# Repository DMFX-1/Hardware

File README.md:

# Hardware
Digital Multi FX Hardware:

DMFX-1 => Motherboard
DMFX-2 => Mezzanine board
Meca => Mechanics
  3D Models => 3D models for electronics 

- Block diagram (image, SVG)
- 3D models (FreeCad, STEP)
- Schematics (Eagle CAD, PDF) 
- PCB layout (Eagle CAD, gerbers)
- BoM (Excel, CSV, text)

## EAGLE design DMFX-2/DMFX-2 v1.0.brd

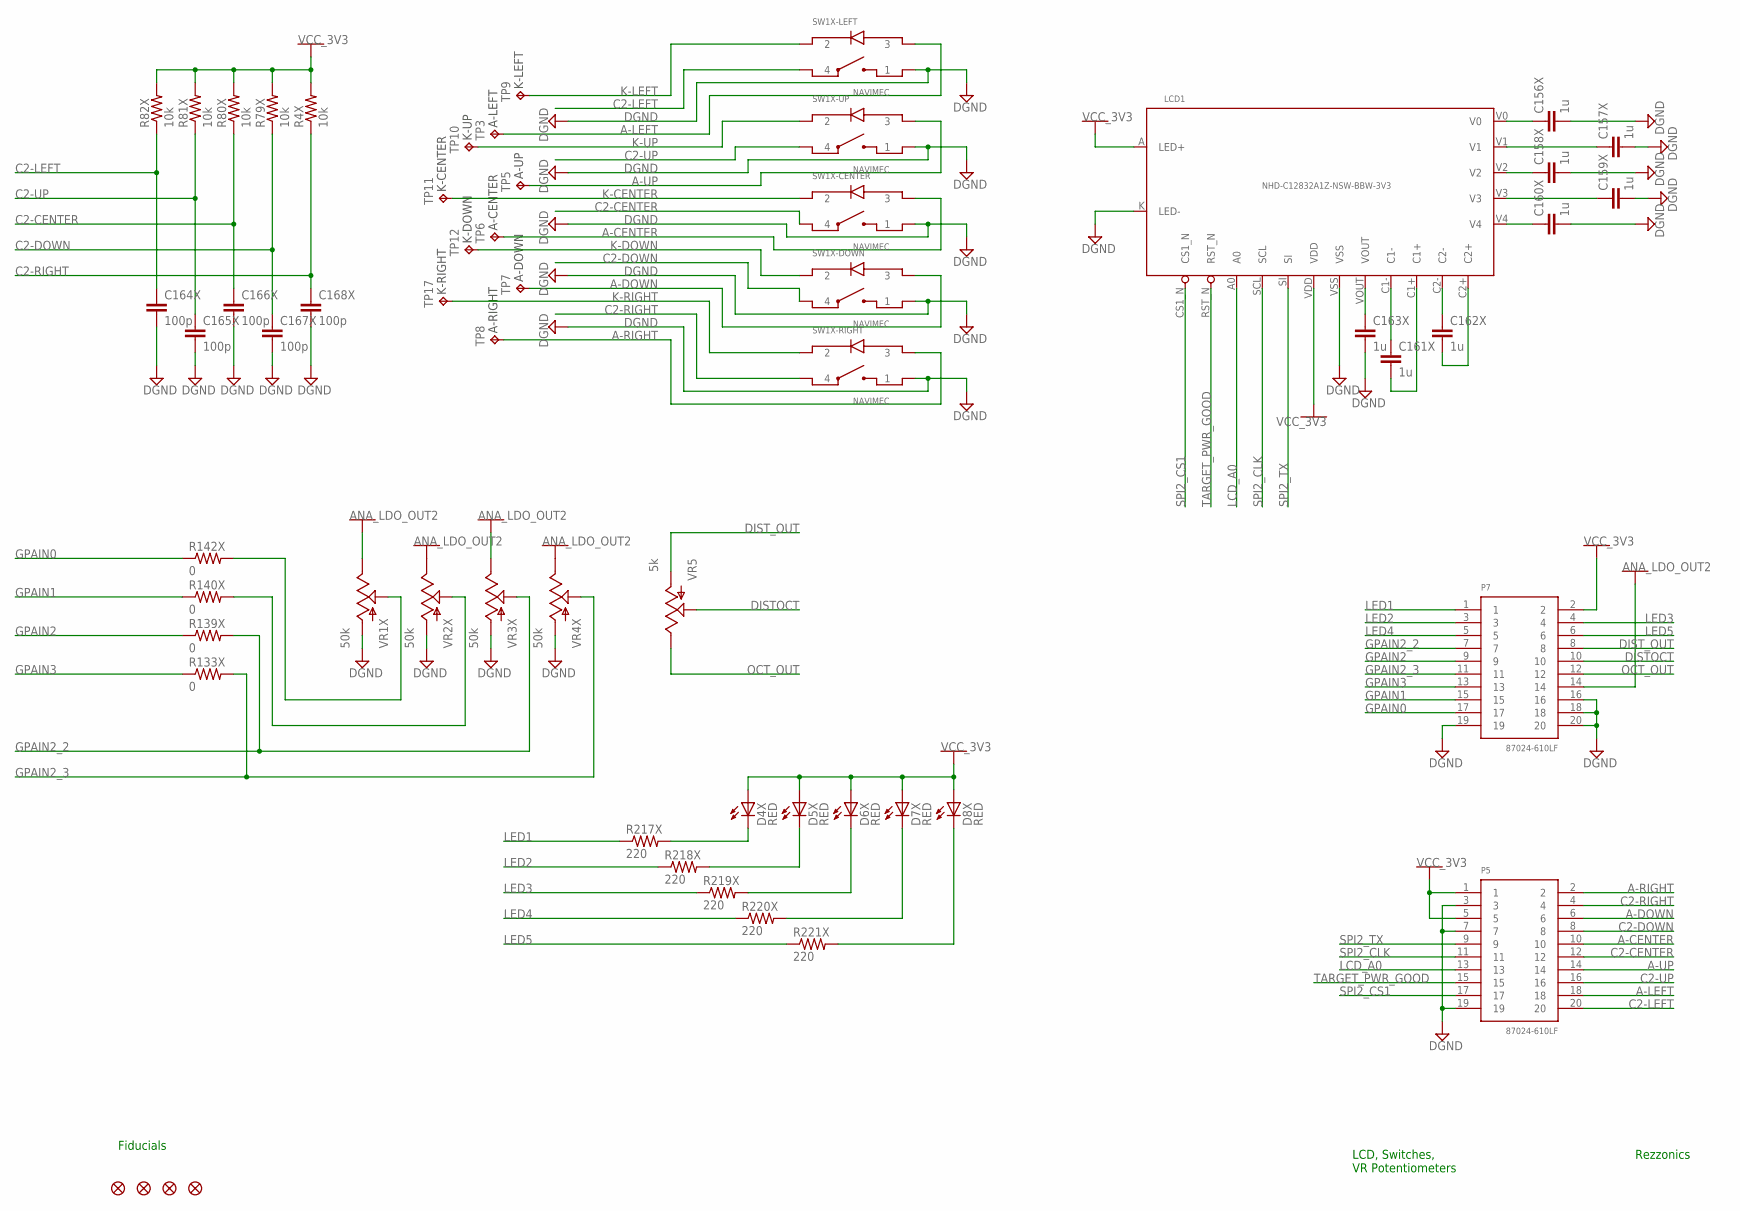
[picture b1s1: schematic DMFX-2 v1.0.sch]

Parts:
C156X, C157X, C158X, C159X, C160X, C161X, C162X, C163X: 1u; C0603K; MPN GRM188R7YA105KA12D
C164X, C165X, C166X, C167X, C168X: 100p; C0402; MPN GRM1555C1H101FA01J
D4X, D5X, D6X, D7X, D8X: RED; LED3MM; MPN LTL-4222N
JP2, JP4, JP5, JP9: FIDUCIAL1X2.5; FIDUCIAL-1X2.5; MPN *
LCD1: NHD-C12832A1Z-NSW-BBW-3V3; NHD-C12832A1Z; MPN NHD-C12832A1Z-NSW-BBW-3V3
P5, P7: 87024-610LF; 87022-110LF; MPN 87024-610LF
R4X, R79X, R80X, R81X, R82X: 10k; 0402-RES; MPN ERJ-2RKF1002X
R133X, R139X, R140X, R142X: 0; 0402-RES; MPN ERJ-2GE0R00X
R217X, R218X, R219X, R220X, R221X: 220; 0402-RES; MPN ERJ-2RKF2200X
SW1X: NAVIMEC; 1ZW0913611806; MPN 1ZW0913611806
TP3, TP5, TP6, TP7, TP8, TP9, TP10, TP11, TP12, TP17: TPTP12R; TP12R; MPN *
VR1X, VR2X, VR3X, VR4X: 50k; ALPS_POT; MPN EVU-F2AF30B54
VR5: 5k; ALPS_POT; MPN EVU-F2AF30B53

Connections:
A-CENTER: P5.10, SW1X.CENTER$3 (3), TP6.TP
A-DOWN: P5.6, SW1X.DOWN$3 (3), TP7.TP
A-LEFT: P5.18, SW1X.LEFT$3 (3), TP3.TP
A-RIGHT: P5.2, SW1X.RIGHT$3 (3), TP8.TP
A-UP: P5.14, SW1X.UP$3 (3), TP5.TP
ANA_LDO_OUT2: P7.14, VR1X.P$1 (E), VR2X.P$1 (E), VR3X.P$1 (E), VR4X.P$1 (E)
C2-CENTER: C166X.1, P5.12, R80X.1, SW1X.CENTER$4 (4)
C2-DOWN: C167X.1, P5.8, R79X.1, SW1X.DOWN$4 (4)
C2-LEFT: C164X.1, P5.20, R82X.1, SW1X.LEFT$4 (4)
C2-RIGHT: C168X.1, P5.4, R4X.1, SW1X.RIGHT$4 (4)
C2-UP: C165X.1, P5.16, R81X.1, SW1X.UP$4 (4)
DGND: C156X.2, C157X.2, C158X.2, C159X.2, C160X.2, C163X.2, C164X.2, C165X.2, C166X.2, C167X.2, C168X.2, LCD1.K (LED-), LCD1.VSS, P5.3, P5.7, P5.19, P7.16, P7.18, P7.19, P7.20, SW1X.CENTER$1 (1), SW1X.DOWN$1 (1), SW1X.LEFT$1 (1), SW1X.RIGHT$1 (1), SW1X.UP$1 (1), VR1X.P$3 (A), VR2X.P$3 (A), VR3X.P$3 (A), VR4X.P$3 (A)
DISTOCT: P7.10, VR5.P$2 (S)
DIST_OUT: P7.8, VR5.P$3 (A)
GPAIN0: P7.17, R142X.1
GPAIN1: P7.15, R140X.1
GPAIN2: P7.9, R139X.1
GPAIN2_0: R142X.2, VR1X.P$2 (S)
GPAIN2_1: R140X.2, VR2X.P$2 (S)
GPAIN2_2: P7.7, R139X.2, VR3X.P$2 (S)
GPAIN2_3: P7.11, R133X.2, VR4X.P$2 (S)
GPAIN3: P7.13, R133X.1
K-CENTER: SW1X.CENTER$2 (2), TP11.TP
K-DOWN: SW1X.DOWN$2 (2), TP12.TP
K-LEFT: SW1X.LEFT$2 (2), TP9.TP
K-RIGHT: SW1X.RIGHT$2 (2), TP17.TP
K-UP: SW1X.UP$2 (2), TP10.TP
LCD_A0: LCD1.A0, P5.13
LCD_C1+: C161X.2, LCD1.C1+
LCD_C1-: C161X.1, LCD1.C1-
LCD_C2+: C162X.2, LCD1.C2+
LCD_C2-: C162X.1, LCD1.C2-
LCD_V0: C156X.1, LCD1.V0
LCD_V1: C157X.1, LCD1.V1
LCD_V2: C158X.1, LCD1.V2
LCD_V3: C159X.1, LCD1.V3
LCD_V4: C160X.1, LCD1.V4
LCD_VOUT: C163X.1, LCD1.VOUT
LED1: P7.1, R217X.1
LED2: P7.3, R218X.1
LED3: P7.4, R219X.1
LED4: P7.5, R220X.1
LED5: P7.6, R221X.1
unnamed: D4X.K (C), R217X.2
unnamed: D5X.K (C), R218X.2
unnamed: D6X.K (C), R219X.2
unnamed: D7X.K (C), R220X.2
unnamed: D8X.K (C), R221X.2
OCT_OUT: P7.12, VR5.P$1 (E)
SPI2_CLK: LCD1.SCL, P5.11
SPI2_CS1: LCD1.CS1_N, P5.17
SPI2_TX: LCD1.SI, P5.9
TARGET_PWR_GOOD: LCD1.RST_N, P5.15
VCC_3V3: D4X.A, D5X.A, D6X.A, D7X.A, D8X.A, LCD1.A (LED+), LCD1.VDD, P5.1, P5.5, P7.2, R4X.2, R79X.2, R80X.2, R81X.2, R82X.2

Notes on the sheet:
Rezzonics
LCD, Switches, VR Potentiometers
Fiducials

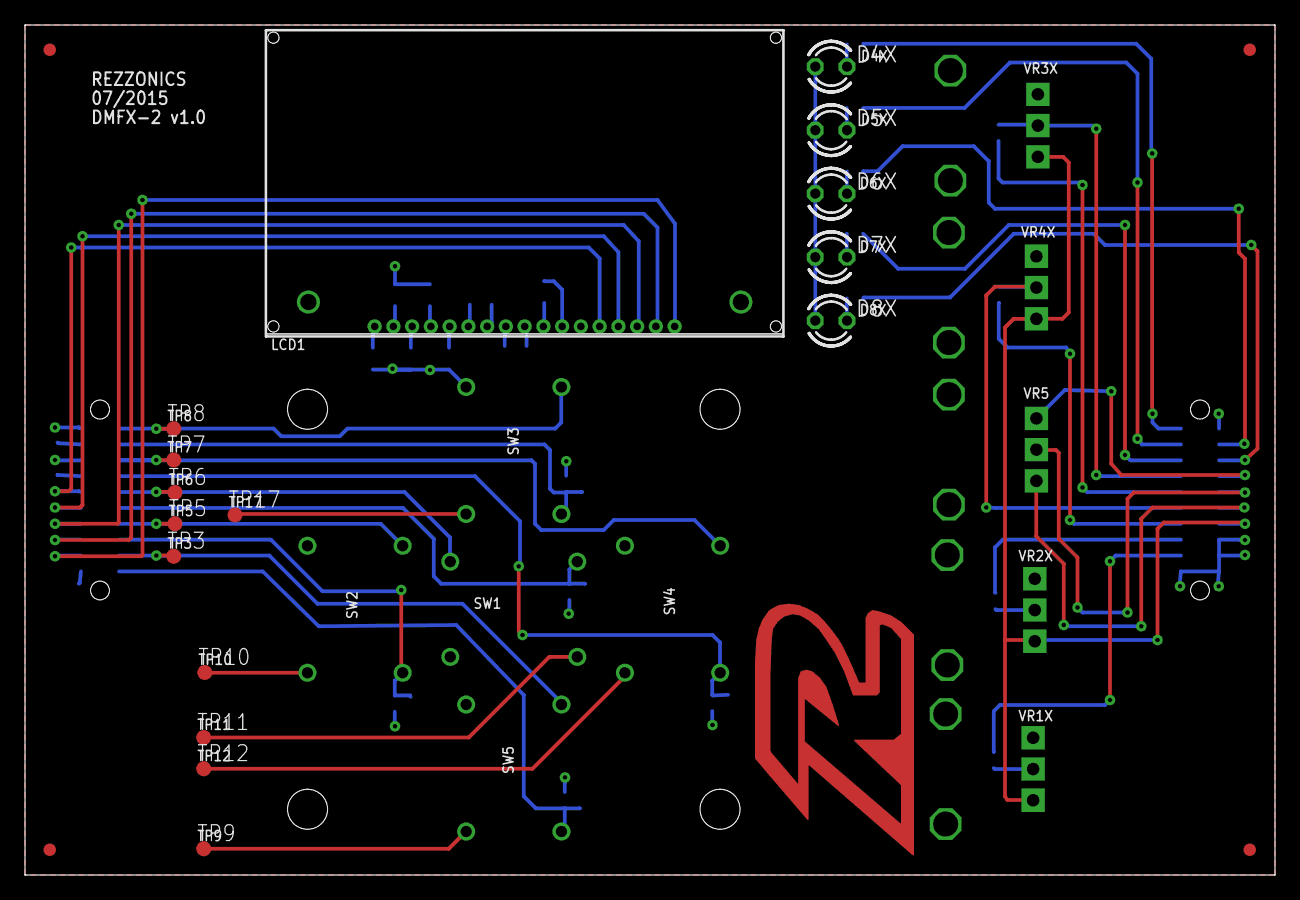
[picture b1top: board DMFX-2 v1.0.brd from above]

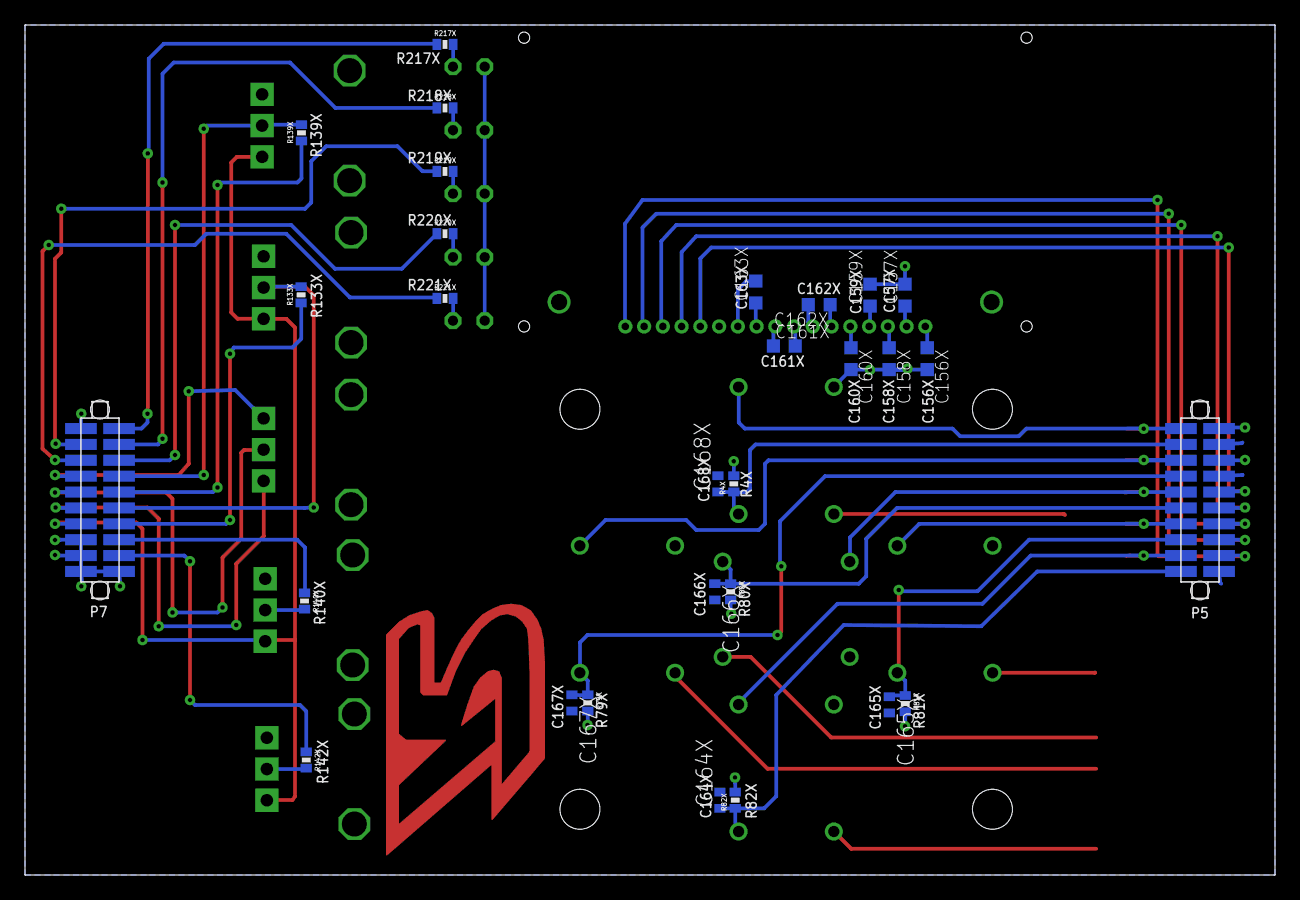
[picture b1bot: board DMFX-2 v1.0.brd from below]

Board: 2 copper layers, 100.0 x 68.0 mm, 56 parts (29 on the bottom side), 54 nets.

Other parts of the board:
U$1: REZZLOGO

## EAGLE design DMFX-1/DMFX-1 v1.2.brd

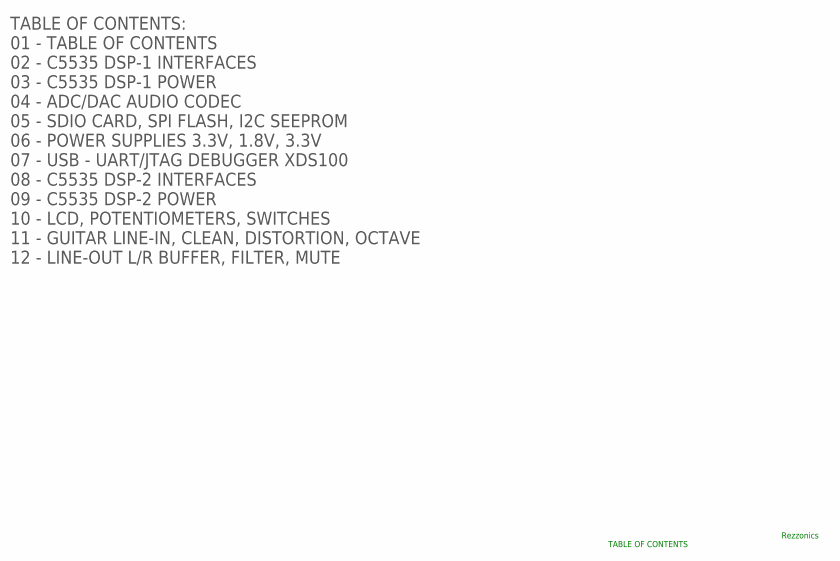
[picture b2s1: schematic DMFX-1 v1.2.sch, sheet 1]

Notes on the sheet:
TABLE OF CONTENTS: 01 - TABLE OF CONTENTS 02 - C5535 DSP-1 INTERFACES 03 - C5535 DSP-1 POWER 04 - ADC/DAC AUDIO CODEC 05 - SDIO CARD, SPI FLASH, I2C SEEPROM 06 - POWER SUPPLIES 3.3V, 1.8V, 3.3V 07 - USB - UART/JTAG DEBUGGER XDS100 08 - C5535 DSP-2 INTERFACES 09 - C5535 DSP-2 POWER 10 - LCD, POTENTI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
Rezzonics
TABLE OF CONTENTS

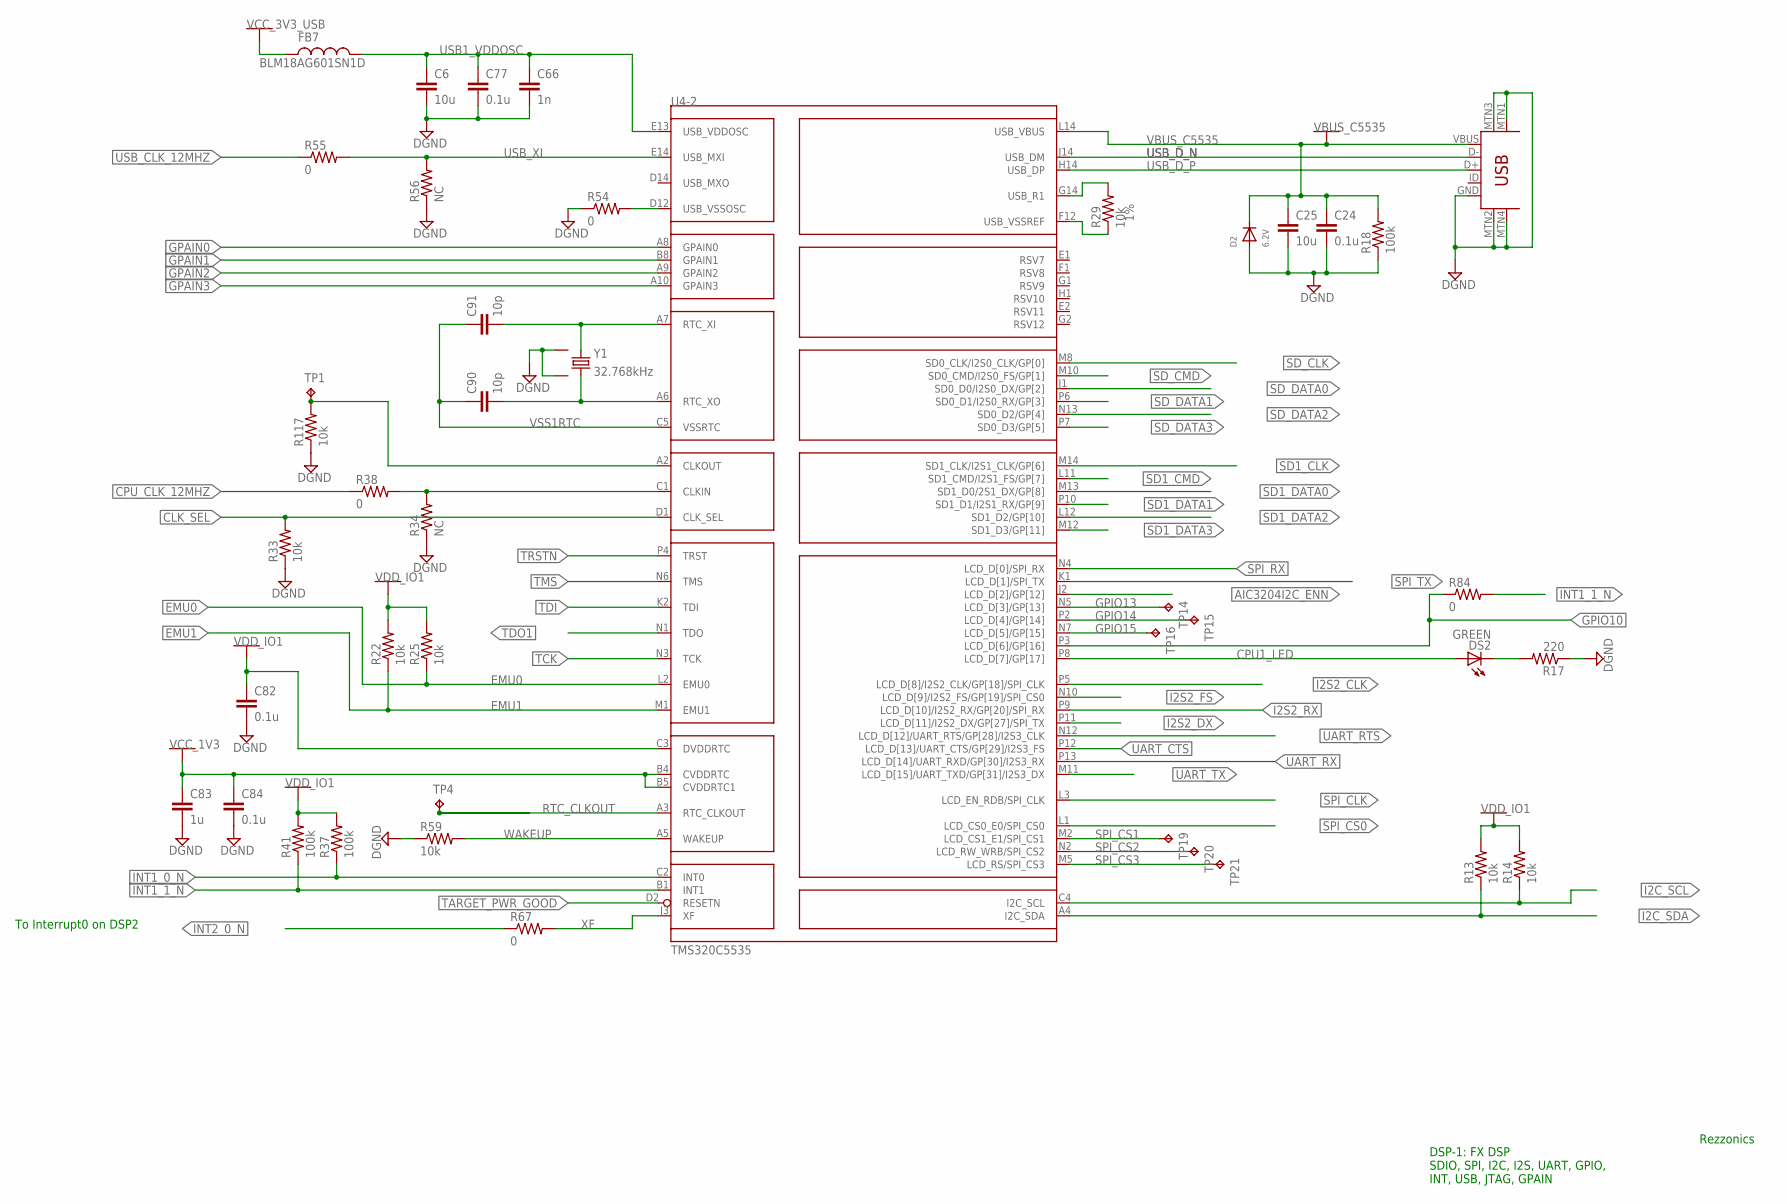
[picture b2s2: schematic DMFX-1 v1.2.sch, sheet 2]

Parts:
C6, C25: 10u; C0603K; MPN GRM188R61C106MA73D
C24, C77: 0.1u; C0402K; MPN GRM155R71C104JA88D
C66: 1n; 0402; MPN GRM155R71H102JA01J
C82, C84: 0.1u; 0402; MPN GRM155R71C104JA88D
C83: 1u; 0402; MPN GRM155R70J105KA12D
C90, C91: 10p; C0402K; MPN GRM1555C1H100FA01D
D2: 6.2V; SMADIODE; MPN 1SMA5920BT3G
DS2: GREEN; CHIPLED_0603; MPN LTST-C190KGKT
FB7: BLM18AG601SN1D; 0805; MPN BLM21AG151SN1D
J1: USB-MINIB-5PIN; USB-MINIB; MPN 10033526-N3212LF
R13, R14, R22, R25, R33, R59, R117: 10k; 0402-RES; MPN ERJ-2RKF1002X
R17: 220; 0402-RES; MPN ERJ-2RKF2200X
R18, R37, R41: 100k; 0402-RES; MPN ERJ-2RKF1003X
R29: 10k; 0402; TOLERANCE 1%; MPN ERJ-2RKF1002X
R34: NC; 0402; MPN *
R38, R54, R67: 0; 0402; MPN ERJ-2GE0R00X
R55, R84: 0; 0402-RES; MPN ERJ-2GE0R00X
R56: NC; 0402-RES; MPN *
TP1, TP4, TP14, TP15, TP16, TP19, TP20, TP21: TPTP06R; TP06R; MPN *
U4: TMS320C5535; PBGA144; MPN TMS320C5535AZHH10
Y1: 32.768kHz; CRYSTAL-32KHZ-SMD_EPSON_MC146; MPN SSPT7F-12.5PF20-R

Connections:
AIC3204I2C_ENN: U4.J2 (LCD_D[2]/GP[12]); also elsewhere on the board
CLK_SEL: R33.2, U4.D1 (CLK_SEL)
CPU1_LED: DS2.A, U4.P8 (LCD_D[7]/GP[17])
CPU_CLK_12MHZ: R38.1; also elsewhere on the board
DGND: C6.2, C24.2, C25.2, C66.2, C77.2, C82.2, C83.2, C84.2, D2.A, J1.GND, J1.MTN1 (MTN2), J1.MTN2 (MTN3), J1.MTN3 (MTN1), J1.MTN4, R17.1, R18.1, R33.1, R34.1, R54.1, R56.1, R59.1, R117.1, Y1.NC1 (3), Y1.NC2 (4); also elsewhere on the board
EMU0: R25.1, U4.L2 (EMU0); also elsewhere on the board
EMU1: R22.1, U4.M1 (EMU1); also elsewhere on the board
GPAIN0: U4.A8 (GPAIN0); also elsewhere on the board
GPAIN1: U4.B8 (GPAIN1); also elsewhere on the board
GPAIN2: U4.A9 (GPAIN2); also elsewhere on the board
GPAIN3: U4.A10 (GPAIN3); also elsewhere on the board
GPIO10: R84.1, U4.P3 (LCD_D[6]/GP[16])
GPIO13: TP14.TP, U4.N5 (LCD_D[3]/GP[13])
GPIO14: TP15.TP, U4.P2 (LCD_D[4]/GP[14])
GPIO15: TP16.TP, U4.N7 (LCD_D[5]/GP[15])
I2C_SCL: R14.1, U4.C4 (I2C_SCL); also elsewhere on the board
I2C_SDA: R13.1, U4.A4 (I2C_SDA); also elsewhere on the board
I2S2_CLK: U4.P5 (LCD_D[8]/I2S2_CLK/GP[18]/SPI_CLK); also elsewhere on the board
I2S2_DX: U4.P11 (LCD_D[11]/I2S2_DX/GP[27]/SPI_TX); also elsewhere on the board
I2S2_FS: U4.N10 (LCD_D[9]/I2S2_FS/GP[19]/SPI_CS0); also elsewhere on the board
I2S2_RX: U4.P9 (LCD_D[10]/I2S2_RX/GP[20]/SPI_RX); also elsewhere on the board
INT1_0_N: R37.1, U4.C2 (INT0); also elsewhere on the board
INT1_1_N: R41.1, R84.2, U4.B1 (INT1)
INT2_0_N: R67.1; also elsewhere on the board
unnamed: C91.2, U4.A7 (RTC_XI), Y1.P$2 (2)
unnamed: C90.2, U4.A6 (RTC_XO), Y1.P$1 (1)
unnamed: R117.2, TP1.TP, U4.A2 (CLKOUT)
unnamed: R34.2, R38.2, U4.C1 (CLKIN)
unnamed: DS2.C, R17.2
unnamed: R29.2, U4.G14 (USB_R1)
RTC_CLKOUT: TP4.TP, U4.A3 (RTC_CLKOUT)
SD1_CLK: U4.M14 (SD1_CLK/I2S1_CLK/GP[6]); also elsewhere on the board
SD1_CMD: U4.L11 (SD1_CMD/I2S1_FS/GP[7]); also elsewhere on the board
SD1_DATA0: U4.M13 (SD1_D0/2S1_DX/GP[8]); also elsewhere on the board
SD1_DATA1: U4.P10 (SD1_D1/I2S1_RX/GP[9]); also elsewhere on the board
SD1_DATA2: U4.L12 (SD1_D2/GP[10]); also elsewhere on the board
SD1_DATA3: U4.M12 (SD1_D3/GP[11]); also elsewhere on the board
SD_CLK: U4.M8 (SD0_CLK/I2S0_CLK/GP[0]); also elsewhere on the board
SD_CMD: U4.M10 (SD0_CMD/I2S0_FS/GP[1]); also elsewhere on the board
SD_DATA0: U4.J1 (SD0_D0/I2S0_DX/GP[2]); also elsewhere on the board
SD_DATA1: U4.P6 (SD0_D1/I2S0_RX/GP[3]); also elsewhere on the board
SD_DATA2: U4.N13 (SD0_D2/GP[4]); also elsewhere on the board
SD_DATA3: U4.P7 (SD0_D3/GP[5]); also elsewhere on the board
SPI_CLK: U4.L3 (LCD_EN_RDB/SPI_CLK); also elsewhere on the board
SPI_CS0: U4.L1 (LCD_CS0_E0/SPI_CS0); also elsewhere on the board
SPI_CS1: TP19.TP, U4.M2 (LCD_CS1_E1/SPI_CS1)
SPI_CS2: TP20.TP, U4.N2 (LCD_RW_WRB/SPI_CS2)
SPI_CS3: TP21.TP, U4.M5 (LCD_RS/SPI_CS3)
SPI_RX: U4.N4 (LCD_D[0]/SPI_RX); also elsewhere on the board
SPI_TX: U4.K1 (LCD_D[1]/SPI_TX); also elsewhere on the board
TARGET_PWR_GOOD: U4.D2 (RESETN); also elsewhere on the board
TCK: U4.N3 (TCK); also elsewhere on the board
TDI: U4.K2 (TDI); also elsewhere on the board
TDO1: U4.N1 (TDO); also elsewhere on the board
TMS: U4.N6 (TMS); also elsewhere on the board
TRSTN: U4.P4 (TRST); also elsewhere on the board
UART_CTS: U4.P12 (LCD_D[13]/UART_CTS/GP[29]/I2S3_FS); also elsewhere on the board
UART_RTS: U4.N12 (LCD_D[12]/UART_RTS/GP[28]/I2S3_CLK); also elsewhere on the board
UART_RX: U4.P13 (LCD_D[14]/UART_RXD/GP[30]/I2S3_RX); also elsewhere on the board
UART_TX: U4.M11 (LCD_D[15]/UART_TXD/GP[31]/I2S3_DX); also elsewhere on the board
USB1_VDDOSC: C6.1, C66.1, C77.1, FB7.2, U4.E13 (USB_VDDOSC)
USB1_VSSOSC: R54.2, U4.D12 (USB_VSSOSC)
USB1_VSSREF: R29.1, U4.F12 (USB_VSSREF)
USB_CLK_12MHZ: R55.1; also elsewhere on the board
USB_D_N: J1.D-, U4.J14 (USB_DM)
USB_D_P: J1.D+, U4.H14 (USB_DP)
USB_XI: R55.2, R56.2, U4.E14 (USB_MXI)
VBUS_C5535: C24.1, C25.1, D2.C, J1.VBUS, R18.2, U4.L14 (USB_VBUS); also elsewhere on the board
VCC_1V3: C83.1, C84.1, U4.B4 (CVDDRTC), U4.B5 (CVDDRTC1); also elsewhere on the board
VCC_3V3_USB: FB7.1; also elsewhere on the board
VDD_IO1: C82.1, R13.2, R14.2, R22.2, R25.2, R37.2, R41.2, U4.C3 (DVDDRTC); also elsewhere on the board
VSS1RTC: C90.1, C91.1, U4.C5 (VSSRTC)
WAKEUP: R59.2, U4.A5 (WAKEUP)
XF: R67.2, U4.J3 (XF)

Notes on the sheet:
To Interrupt0 on DSP2
Rezzonics
DSP-1: FX DSP SDIO, SPI, I2C, I2S, UART, GPIO, INT, USB, JTAG, GPAIN

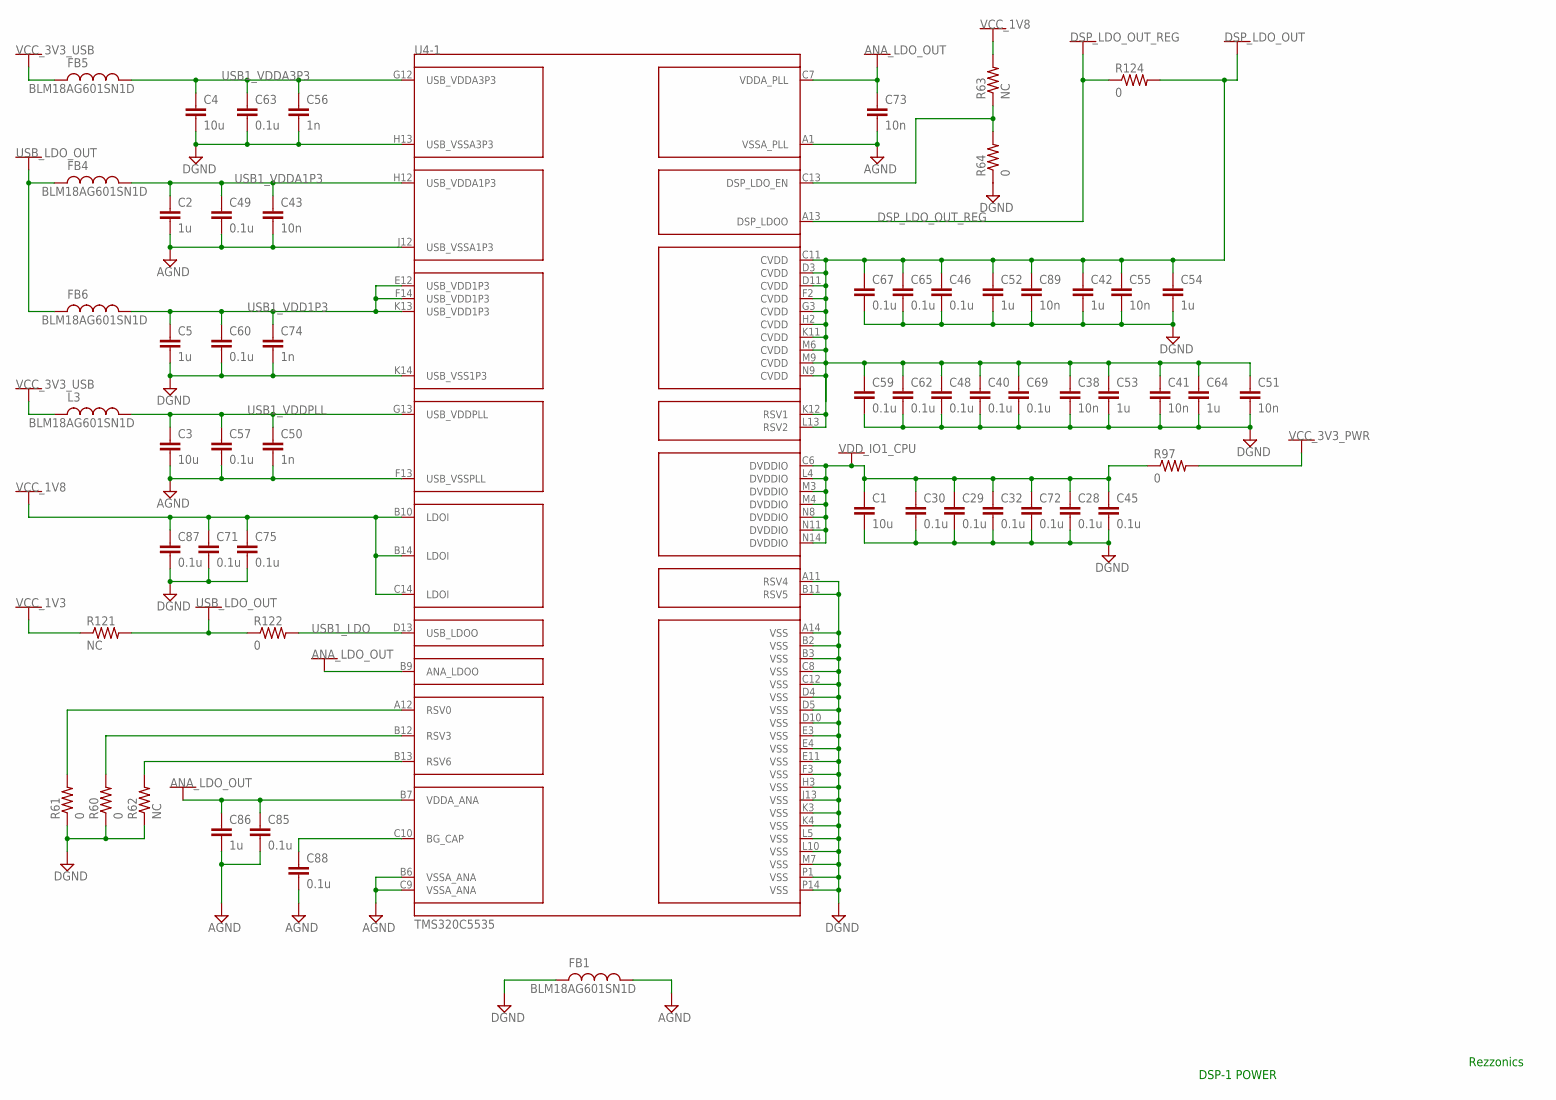
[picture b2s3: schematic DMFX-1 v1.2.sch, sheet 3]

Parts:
C1, C3, C4: 10u; C0603K; MPN GRM188R61C106MA73D
C2, C5: 1u; C0402K; MPN GRM155R70J105KA12D
C28, C29, C30: 0.1u; C0402K; MPN GRM155R71C104JA88D
C32, C40, C45, C46, C48, C49, C57, C59, C60, C62, C63, C65, C67, C69, C71, C72, C75, C85, C87, C88: 0.1u; 0402; MPN GRM155R71C104JA88D
C38, C41, C43, C51, C55, C73: 10n; 0402; MPN GRM155R71E103KA01D
C42, C52, C53, C54, C64, C86: 1u; 0402; MPN GRM155R70J105KA12D
C50, C56: 1n; 0402; MPN GRM155R71H102JA01J
C74: 1n; C0402K; MPN GRM155R71H102JA01J
C89: 10n; C0402K; MPN GRM155R71E103KA01D
FB1, FB4, FB5, FB6: BLM18AG601SN1D; 0603; MPN BLM18AG601SN1D
L3: BLM18AG601SN1D; 0603; MPN BLM18AG601SN1D
R60, R61, R64: 0; 0402-RES; MPN ERJ-2GE0R00X
R62, R63: NC; 0402-RES; MPN *
R97: 0; 0805; MPN ERJ-2GE0R00X
R121: NC; 0805; MPN *
R122, R124: 0; 0805; MPN ERJ-6GEY0R00V
U4: TMS320C5535; PBGA144; MPN TMS320C5535AZHH10

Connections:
AGND: C2.2, C3.2, C43.2, C49.2, C50.2, C57.2, C73.2, C85.2, C86.2, C88.2, FB1.2, U4.A1 (VSSA_PLL), U4.B6 (VSSA_ANA), U4.C9 (VSSA_ANA), U4.F13 (USB_VSSPLL), U4.J12 (USB_VSSA1P3); also elsewhere on the board
ANA_LDO_OUT: C73.1, C85.1, C86.1, U4.B7 (VDDA_ANA), U4.B9 (ANA_LDOO), U4.C7 (VDDA_PLL)
DGND: C1.2, C4.2, C5.2, C28.2, C29.2, C30.2, C32.2, C38.2, C40.2, C41.2, C42.2, C45.2, C46.2, C48.2, C51.2, C52.2, C53.2, C54.2, C55.2, C56.2, C59.2, C60.2, C62.2, C63.2, C64.2, C65.2, C67.2, C69.2, C71.2, C72.2, C74.2, C75.2, C87.2, C89.2, FB1.1, R60.1, R61.1, R62.1, R64.1, U4.A11 (RSV4), U4.A14 (VSS), U4.B2 (VSS), U4.B3 (VSS), U4.B11 (RSV5), U4.C8 (VSS), U4.C12 (VSS), U4.D4 (VSS), U4.D5 (VSS), U4.D10 (VSS), U4.E3 (VSS), U4.E4 (VSS), U4.E11 (VSS), U4.F3 (VSS), U4.H3 (VSS), U4.H13 (USB_VSSA3P3), U4.J13 (VSS), U4.K3 (VSS), U4.K4 (VSS), U4.K14 (USB_VSS1P3), U4.L5 (VSS), U4.L10 (VSS), U4.M7 (VSS), U4.P1 (VSS), U4.P14 (VSS); also elsewhere on the board
DSP_LDO_OUT: C38.1, C40.1, C41.1, C42.1, C46.1, C48.1, C51.1, C52.1, C53.1, C54.1, C55.1, C59.1, C62.1, C64.1, C65.1, C67.1, C69.1, C89.1, R124.2, U4.C11 (CVDD), U4.D3 (CVDD), U4.D11 (CVDD), U4.F2 (CVDD), U4.G3 (CVDD), U4.H2 (CVDD), U4.K11 (CVDD), U4.K12 (RSV1), U4.L13 (RSV2), U4.M6 (CVDD), U4.M9 (CVDD), U4.N9 (CVDD)
DSP_LDO_OUT_REG: R124.1, U4.A13 (DSP_LDOO)
unnamed: R63.1, R64.2, U4.C13 (DSP_LDO_EN)
unnamed: R61.2, U4.A12 (RSV0)
unnamed: R60.2, U4.B12 (RSV3)
unnamed: R62.2, U4.B13 (RSV6)
unnamed: C88.1, U4.C10 (BG_CAP)
USB1_LDO: R122.2, U4.D13 (USB_LDOO)
USB1_VDD1P3: C5.1, C60.1, C74.1, FB6.2, U4.E12 (USB_VDD1P3), U4.F14 (USB_VDD1P3), U4.K13 (USB_VDD1P3)
USB1_VDDA1P3: C2.1, C43.1, C49.1, FB4.2, U4.H12 (USB_VDDA1P3)
USB1_VDDA3P3: C4.1, C56.1, C63.1, FB5.2, U4.G12 (USB_VDDA3P3)
USB1_VDDPLL: C3.1, C50.1, C57.1, L3.2, U4.G13 (USB_VDDPLL)
USB_LDO_OUT: FB4.1, FB6.1, R121.2, R122.1
VCC_1V3: R121.1; also elsewhere on the board
VCC_1V8: C71.1, C75.1, C87.1, R63.2, U4.B10 (LDOI), U4.B14 (LDOI), U4.C14 (LDOI); also elsewhere on the board
VCC_3V3_PWR: R97.2; also elsewhere on the board
VCC_3V3_USB: FB5.1, L3.1; also elsewhere on the board
VDD_IO1_CPU: C1.1, C28.1, C29.1, C30.1, C32.1, C45.1, C72.1, R97.1, U4.C6 (DVDDIO), U4.L4 (DVDDIO), U4.M3 (DVDDIO), U4.M4 (DVDDIO), U4.N8 (DVDDIO), U4.N11 (DVDDIO), U4.N14 (DVDDIO)

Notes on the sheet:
DSP-1 POWER
Rezzonics

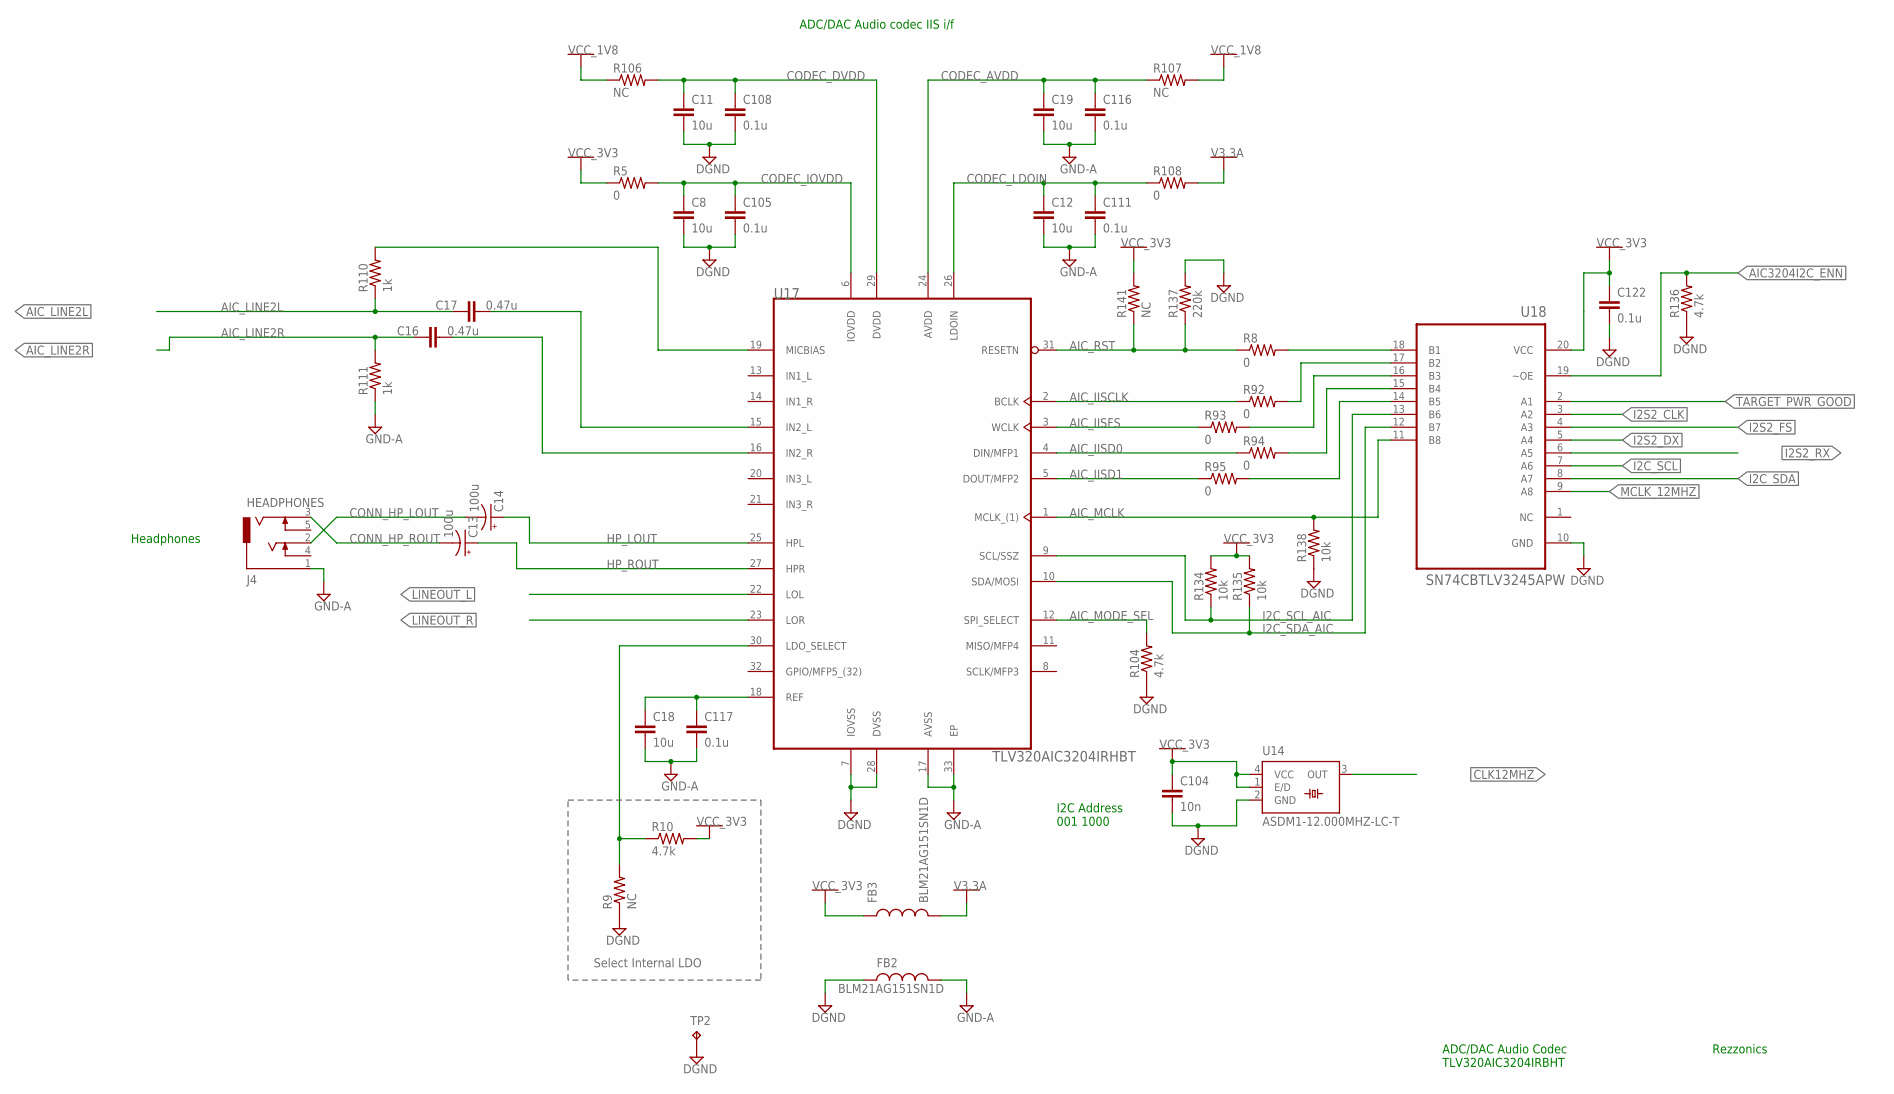
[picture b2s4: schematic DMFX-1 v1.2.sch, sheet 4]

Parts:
C8, C11, C12, C18, C19: 10u; C0603K; MPN GRM188R61C106MA73D
C13, C14: 100u; 1411; MPN ATCC-211B-010-107M-T
C16, C17: 0.47u; C0603K; MPN GRM188R71C474KA88D
C104: 10n; C0402K; MPN GRM155R71E103KA01D
C105, C108, C111, C116, C117, C122: 0.1u; C0402K; MPN GRM155R71C104JA88D
FB2, FB3: BLM21AG151SN1D; 0805; MPN BLM21AG151SN1D
J4: HEADPHONES; AUDIO-JACK-3.5MM-SMD; MPN SJ1-3515-SMT-TR
R5, R8, R92, R93, R94, R95, R108: 0; 0402-RES; MPN ERJ-2GE0R00X
R9: NC; 0603-RES; MPN *
R10: 4.7k; 0603-RES; MPN ERJ-3EKF4701V
R104, R136: 4.7k; 0402-RES; MPN ERJ-2RKF4701X
R106, R107, R141: NC; 0402-RES; MPN *
R110, R111: 1k; 0402-RES; MPN ERJ-2RKF1001X
R134, R135, R138: 10k; 0402-RES; MPN ERJ-2RKF1002X
R137: 220k; 0402-RES; MPN ERJ-2RKF2203X
TP2: TPTP06R; TP06R; MPN *
U14: ASDM1-12.000MHZ-LC-T; ASDM1; MPN ASDM1-12.000MHZ-LC-T
U17: TLV320AIC3204IRHBT; QFN50P500X500X100-33N; MPN TLV320AIC3204IRHBT
U18: SN74CBTLV3245APW; SOP65P640X120-20N; MPN SN74CBTLV3245APWR

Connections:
AIC3204I2C_ENN: R136.2, U18.19 (~OE); also elsewhere on the board
AIC_IISCLK: R92.1, U17.2 (BCLK)
AIC_IISD0: R94.1, U17.4 (DIN/MFP1)
AIC_IISD1: R95.1, U17.5 (DOUT/MFP2)
AIC_IISFS: R93.1, U17.3 (WCLK)
AIC_LINE2L: C17.1, R110.1; also elsewhere on the board
AIC_LINE2R: C16.1, R111.2; also elsewhere on the board
AIC_MCLK: R138.2, U17.1 (MCLK_(1)), U18.11 (B8)
AIC_MODE_SEL: R104.2, U17.12 (SPI_SELECT)
AIC_RST: R8.1, R137.1, R141.1, U17.31 (RESETN)
CLK12MHZ: U14.3 (OUT); also elsewhere on the board
CODEC_AVDD: C19.1, C116.1, R107.1, U17.24 (AVDD)
CODEC_DVDD: C11.1, C108.1, R106.2, U17.29 (DVDD)
CODEC_IOVDD: C8.1, C105.1, R5.2, U17.6 (IOVDD)
CODEC_LDOIN: C12.1, C111.1, R108.1, U17.26 (LDOIN)
CONN_HP_LOUT: C14.-, J4.2 (T)
CONN_HP_ROUT: C13.-, J4.3 (R)
DGND: C8.2, C11.2, C104.2, C105.2, C108.2, C122.2, FB2.1, R9.1, R104.1, R136.1, R137.2, R138.1, TP2.TP, U14.2 (GND), U17.7 (IOVSS), U17.28 (DVSS), U18.10 (GND); also elsewhere on the board
GND-A: C12.2, C18.2, C19.2, C111.2, C116.2, C117.2, FB2.2, J4.1 (S), R111.1, U17.17 (AVSS), U17.33 (EP); also elsewhere on the board
HP_LOUT: C14.+, U17.25 (HPL)
HP_ROUT: C13.+, U17.27 (HPR)
I2C_SCL: U18.7 (A6); also elsewhere on the board
I2C_SCL_AIC: R134.1, U17.9 (SCL/SSZ), U18.13 (B6)
I2C_SDA: U18.8 (A7); also elsewhere on the board
I2C_SDA_AIC: R135.1, U17.10 (SDA/MOSI), U18.12 (B7)
I2S2_CLK: U18.3 (A2); also elsewhere on the board
I2S2_DX: U18.5 (A4); also elsewhere on the board
I2S2_FS: U18.4 (A3); also elsewhere on the board
I2S2_RX: U18.6 (A5); also elsewhere on the board
LINEOUT_L: U17.22 (LOL); also elsewhere on the board
LINEOUT_R: U17.23 (LOR); also elsewhere on the board
MCLK_12MHZ: U18.9 (A8); also elsewhere on the board
unnamed: C17.2, U17.15 (IN2_L)
unnamed: C16.2, U17.16 (IN2_R)
unnamed: R9.2, R10.1, U17.30 (LDO_SELECT)
unnamed: C18.1, C117.1, U17.18 (REF)
unnamed: R8.2, U18.18 (B1)
unnamed: R92.2, U18.17 (B2)
unnamed: R93.2, U18.16 (B3)
unnamed: R94.2, U18.15 (B4)
unnamed: R95.2, U18.14 (B5)
unnamed: R110.2, U17.19 (MICBIAS)
TARGET_PWR_GOOD: U18.2 (A1); also elsewhere on the board
V3.3A: FB3.2, R108.2; also elsewhere on the board
VCC_1V8: R106.1, R107.2; also elsewhere on the board
VCC_3V3: C104.1, C122.1, FB3.1, R5.1, R10.2, R134.2, R135.2, R141.2, U14.1 (E/D), U14.4 (VCC), U18.20 (VCC); also elsewhere on the board

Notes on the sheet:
Select Internal LDO
Headphones
I2C Address 001 1000
ADC/DAC Audio codec IIS i/f
Rezzonics
ADC/DAC Audio Codec TLV320AIC3204IRBHT

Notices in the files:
parts and their libraries:
SparkFun: Licensing: CC v3.0 Share-Alike You are welcome to use this library for commercial purposes.
